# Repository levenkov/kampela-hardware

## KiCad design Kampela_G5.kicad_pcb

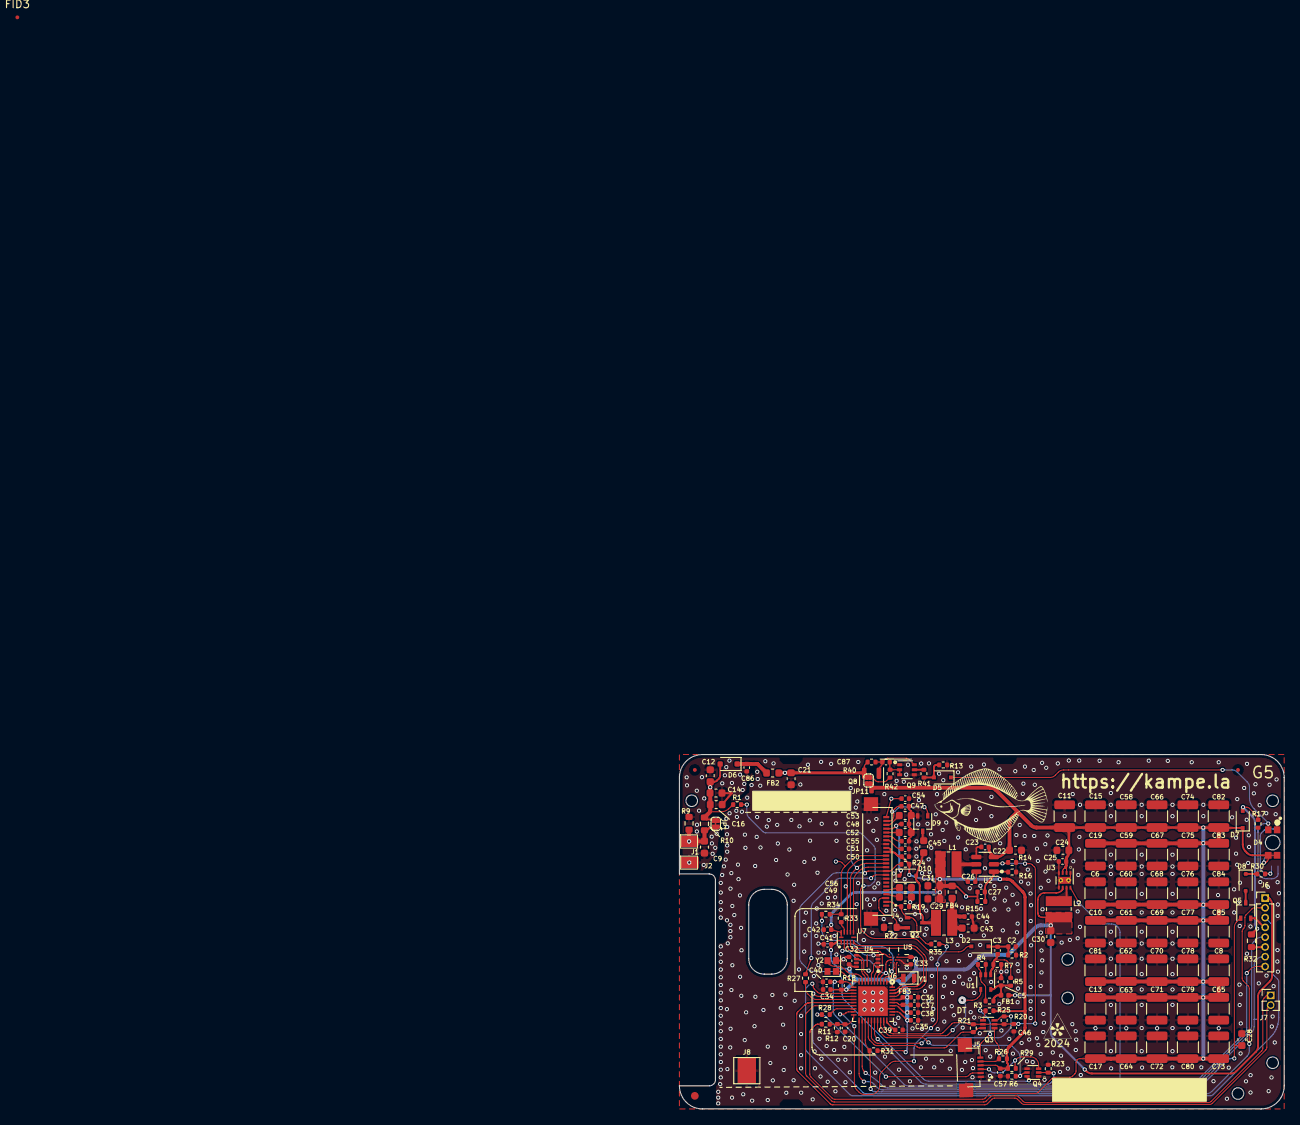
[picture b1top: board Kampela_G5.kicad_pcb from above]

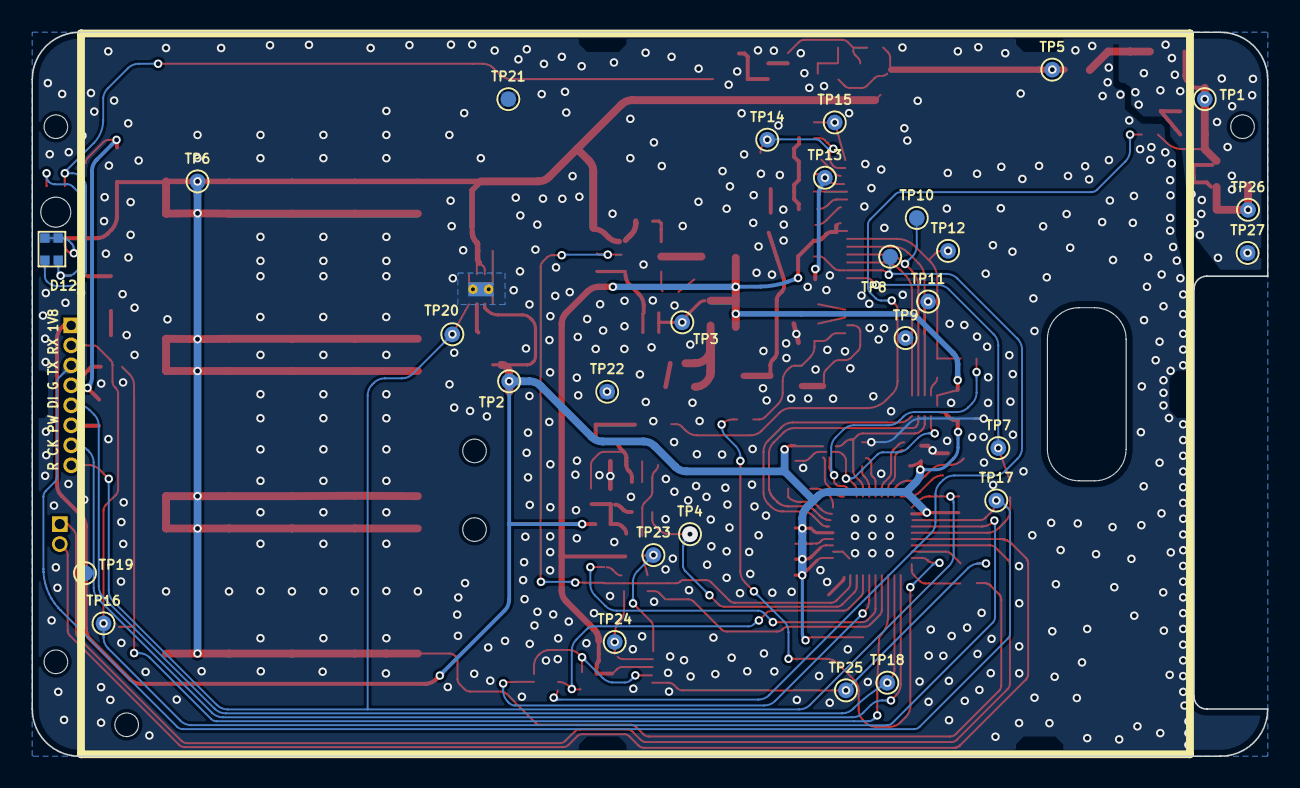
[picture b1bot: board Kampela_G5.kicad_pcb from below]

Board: 2 copper layers, 78.5 x 46.0 mm, 194 parts (28 on the bottom side), 86 nets.

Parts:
C2, C3, C27: 100p; C_0402_1005Metric
C5, C20, C23, C25, C26, C32, C33, C35, C36, C37, C38, C40, C41, C42, C46: 0.1u; C_0402_1005Metric
C6, C8, C10, C11, C13, C15, C17, C19, C58, C59, C60, C61, C62, C63, C64, C65, C66, C67, C68, C69, C70, C71, C72, C73, C74, C75, C76, C77, C78, C79, C80, C81, C82, C83, C84, C85: 47x16; C_1210_3225Metric
C9: 15p; C_0603_1608Metric
C12, C14: 47; C_0603_1608Metric
C16: 100; C_0603_1608Metric
C21: 10x25; C_0603_1608Metric
C22, C24: 10x16; C_0603_1608Metric
C28, C43, C45, C49, C52, C53, C56: 4.7x25; C_0603_1608Metric
C29, C30, C31: 22x6.3; C_0603_1608Metric
C34, C39, C50, C51, C55, C57: 1x6.3; C_0402_1005Metric
C44: 0.1; C_0402_1005Metric
C47, C48, C54, C86, C87: 1x50; C_0402_1005Metric
D2, D7, D10: BAT54WS; D_SOD-323F
D4: 156125RG73000; SMD4_WL-SBRW-1205_REV-MOUNT_WRE
D5: D3Z13BF-7; D_SOD-323F
D6: BAS70WS; D_SOD-323F
D8: D3Z5V1BF-7; D_SOD-323F
D9: BAS70-04W; SOT-323_SC-70
D12: SB0603WC01-RG; LED_DUAL_0603
FB1, FB3: BLM15AG102SZ1D; L_0402_1005Metric
FB2, FB4: BLM18KG102SN1D; L_0603_1608Metric
FID1, FID2, FID3, FID4: Fiducial; Fiducial_0.5mm_Mask1.5mm
H1, H2, H3: MountingHole; MountingHole_2.1mm
J1, J2, J8: E_ANT; TestPoint_Pad_2.4x3.5mm
J4: E2154CS0C1; GDEY027T91-T01_bended
J5: TOUCH; HRS_FH34SRJ-6S-0.5SH(50)
J6: Conn_01x08; PinHeader_1x08_P1.27mm_Vertical
J7: Conn_01x02; PinHeader_1x02_P1.27mm_Vertical
JP1, JP11: SolderJumper_2_Open; SolderJumper_0.8.x1mm
L1: 3.3uH; L_Wuerth_MAPI-3015
L2: 2.2uH; L_Wuerth_MAPI-3015
L3: NR3015T100M; L_Wuerth_MAPI-3015
Q2: PMF250XNEX; SOT-323_SC-70
Q3, Q4: SSM6N35AFE; SOT-563
Q5: NX138BKWX; SOT-323_SC-70
Q8: NTR5105PT1G; SOT-23
Q9: BC846BS; SOT-363_SC-70-6
R1, R6, R17, R18, R23, R24, R25, R26, R27, R28, R29: 10K; R_0402_1005Metric
R2, R3, R16: 52.3K; R_0402_1005Metric
R4, R41: 47K; R_0402_1005Metric
R5, R7, R40, R42: 100K; R_0402_1005Metric
R9: 1K; R_0603_1608Metric
R10, R32: 2.2; R_0603_1608Metric
R11: 976K; R_0402_1005Metric
R12, R14: 150K; R_0402_1005Metric
R13, R20, R21, R34, R35: 1K; R_0402_1005Metric
R15: 130K; R_0402_1005Metric
R19, R31: 470K; R_0402_1005Metric
R22: 0.47R; R_0603_1608Metric
R30, R33: 100; R_0402_1005Metric
TP1, TP2, TP3, TP4, TP5, TP6, TP7, TP8, TP9, TP10, TP11, TP12, TP13, TP14, TP15, TP16, TP17, TP18, TP19, TP20, TP21, TP22, TP23, TP24, TP25, TP26, TP27: TestPoint; TestPoint_Pad_D1.0mm
U1: LMV7271; SOT-353_SC-70-5
U2: AP63200WU; TSOT-23-6
U3: TPS62171DSG; WSON-8-1EP_2x2mm_P0.5mm_EP0.9x1.6mm_ThermalVias
U4: APS6404L-SQN; SON-8-1EP_3x2mm_P0.5mm_EP1.4x1.6mm
U5: AT25XE321D-UUN-T; WLCSP 12-ball 3 x 2 x 3 Array
U6: EFM32PG23B200F512IM40; QFN-40_EP_5x5_Pitch0.4mm
U7: TXU0104PW; Texas_R-PUQFN-N12
Y1: FC2012AN; Crystal_SMD_2012-2Pin_2.0x1.2mm
Y2: 39MHz; Crystal_SMD_2016-4Pin_2.0x1.6mm

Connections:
+1V8: C30.2, C32.1, C33.1, C34.2, C35.1, C36.1, C38.1, C41.2, FB1.1, FB3.2, J6.1, L2.2, R18.2, R31.1, TP2.1, U3.6 (VOS), U4.8 (VCC), U5.B2 (VCC), U6.12 (DVDD), U6.32 (VREGVDD), U6.34 (DVDD), U6.36 (IOVDD), U7.1 (VCCA)
+2V8: C27.1, C29.2, C31.2, C42.1, C50.2, C57.1, FB4.2, J4.15, J4.16, J5.4, L1.2, R15.1, R24.2, R25.1, R26.1, R29.2, TP3.1, U7.11 (VCCB), U7.12 (OE)
/Cap Block/HV: C6.2, C8.2, C10.2, C11.2, C13.2, C15.2, C17.2, C19.2, C22.2, C23.1, C24.2, C25.1, C58.2, C59.2, C60.2, C61.2, C62.2, C63.2, C64.2, C65.2, C66.2, C67.2, C68.2, C69.2, C70.2, C71.2, C72.2, C73.2, C74.2, C75.2, C76.2, C77.2, C78.2, C79.2, C80.2, C81.2, C82.2, C83.2, C84.2, C85.2, D4.3 (A2), D4.4 (A1), D7.1 (K), D12.2 (K1), D12.4 (K2), JP11.1 (A), Q8.3 (D), R11.1, TP6.1, U2.3 (IN), U3.2 (VIN), U3.3 (EN)
/Display/2V8_EN: C46.1, Q3.2 (G), Q3.5 (G), R14.2, R20.2, R21.2, U2.2 (EN), U6.29 (PA09)
/Display/BUSY: R27.2, U6.15 (PB04)
/Display/E_BUSY: J4.9, R27.1, TP7.1
/Display/E_CS: U6.38 (PD02), U7.4 (A3)
/Display/E_D/C: U6.37 (PD03), U7.5 (A4)
/Display/E_MISO: R34.1, U5.D4 (IO1/SO), U6.2 (PC01)
/Display/E_RES: J4.10, Q4.6 (D), R24.1, TP8.1
/Display/E_SCK: U5.F2 (SCK), U6.4 (PC03), U7.3 (A2)
/Display/E_SDI: U5.E3 (SI/IO0), U6.3 (PC02), U7.2 (A1)
/Display/GDR: J4.2, Q2.1 (G), R19.1, R35.1
/Display/H_CS: J4.12, TP10.1, U7.8 (B3)
/Display/H_D/C: J4.11, TP9.1, U7.7 (B4)
/Display/H_SCK: J4.13, TP11.1, U7.9 (B2)
/Display/H_SDI: J4.14, R33.1, R34.2, TP12.1
/Display/INT: R28.2, U6.18 (PB01)
/Display/POW: C43.2, C44.1, FB4.1, L3.1
/Display/PREVGH: C48.1, D10.1 (K), J4.21, TP13.1
/Display/PREVGL: C47.1, D9.1, J4.23, TP14.1
/Display/RES: Q4.2 (G), R23.2, U6.26 (PA06)
/Display/RESE: J4.3, Q2.2 (S), R22.1
/Display/RES_TC: Q4.5 (G), R6.2, U6.27 (PA07)
/Display/SCL: Q3.3 (D), R21.1, U6.24 (PA04)
/Display/SDA: Q3.6 (D), R20.1, U6.25 (PA05)
/Display/T_INT: J5.2, R28.1, TP25.1
/Display/T_RES: J5.3, Q4.3 (D), R29.1
/Display/T_SCL: J5.5, Q3.4 (S), R26.2, TP24.1
/Display/T_SDA: J5.6, Q3.1 (S), R25.2, TP23.1
/Display/VCOM: C54.2, J4.24, TP15.1
/MCU/DATA: TP4.1, U1.4, U6.28 (PA08)
/MCU/FLASH_CS: U5.B4 (~CS), U6.1 (PC00)
/MCU/P_GOOD: C40.1, J6.8, R18.1, TP20.1, U3.8 (PG), U6.11 (~RESET)
/MCU/P_IN: J6.6, R32.1
/MCU/RAM_CS: U4.1 (~CE), U6.5 (PC04)
/MCU/RX: J6.2, TP16.1, U6.14 (PB05)
/MCU/R_MISO: U4.2 (SO/SIO), U6.6 (PC05)
/MCU/R_MOSI: U4.5 (SI/SIO), U6.7 (PC06)
/MCU/R_SCK: U4.6 (SCLK), U6.8 (PC07)
/MCU/SWDCK: J6.7, TP19.1, U6.21 (PA01)
/MCU/SWDIO: J6.5, TP18.1, U6.22 (PA02)
/MCU/TX: J6.3, TP17.1, U6.13 (PB06)
/MCU/V_CHK: C20.1, R11.2, R12.1, U6.20 (PA00)
/MCU/~MCU_OK: C28.2, Q5.1 (G), R31.2, U6.23 (PA03)
/Power/IN_DT: C12.1, C14.1, C16.1, D6.2 (A), JP1.1 (A), R1.1, R10.2, TP1.1
GND: C2.2, C5.1, C6.1, C8.1, C9.2, C10.1, C11.1, C12.2, C13.1, C14.2, C15.1, C16.2, C17.1, C19.1, C20.2, C21.1, C22.1, C23.2, C24.1, C25.2, C28.1, C29.1, C30.1, C31.1, C32.2, C33.2, C34.1, C35.2, C36.2, C37.2, C38.2, C39.1, C40.2, C41.1, C42.2, C43.1, C44.2, C46.2, C47.2, C48.2, C49.1, C50.1, C51.1, C52.1, C53.1, C54.1, C55.1, C56.1, C57.2, C58.1, C59.1, C60.1, C61.1, C62.1, C63.1, C64.1, C65.1, C66.1, C67.1, C68.1, C69.1, C70.1, C71.1, C72.1, C73.1, C74.1, C75.1, C76.1, C77.1, C78.1, C79.1, C80.1, C81.1, C82.1, C83.1, C84.1, C85.1, C86.2, D9.2, J2.1, J4.8, J4.17, J4.S2 (S), J5.1, J5.S2 (S), J6.4, J8.1, Q4.1 (S), Q4.4 (S), Q5.2 (S), Q9.1 (E1), Q9.4 (E2), R2.2, R4.2, R6.1, R7.2, R9.1, R12.2, R13.2, R14.1, R16.2, R17.2, R19.2, R22.2, R23.1, TP21.1, TP22.1, TP27.1, U1.2 (V-), U2.4 (GND), U3.1 (PGND), U3.4 (AGND), U3.5 (FB), U3.9 (PAD), U4.4 (VSS), U5.C3 (GND), U6.33 (VREGVSS), U6.41 (VSS), U7.6 (GND), Y2.2
unnamed: C45.1, D9.3
unnamed: D2.2 (A), R1.2
unnamed: C2.1, C3.2, D2.1 (K), R2.1
unnamed: D5.2 (A), R13.1, R41.2
unnamed: C86.1, D6.1 (K), FB2.2
unnamed: D7.2 (A), R17.1, R32.2
unnamed: D8.2 (A), Q5.3 (D)
unnamed: D8.1 (K), R30.2
unnamed: C45.2, D10.2 (A), L3.2, Q2.3 (D)
unnamed: D4.2 (K2), D5.1 (K), D12.1 (A1)
unnamed: D4.1 (K1), D12.3 (A2), R30.1
unnamed: C9.1, J1.1, JP1.2 (B), R9.2, R10.1, TP26.1
unnamed: C49.2, J4.4
unnamed: C56.2, J4.5
unnamed: C51.2, J4.18
unnamed: C55.2, J4.19
unnamed: C52.2, J4.20
unnamed: C53.2, J4.22
unnamed: J7.1, U6.17 (PB02)
unnamed: J7.2, U6.16 (PB03)
unnamed: C21.2, FB2.1, JP11.2 (B), Q8.2 (S), R40.1, R42.1, TP5.1
unnamed: C87.1, Q8.1 (G), Q9.6 (C1), R40.2
unnamed: C87.2, Q9.2 (B1), Q9.3 (C2), R42.2
unnamed: Q9.5 (B2), R41.1
unnamed: C3.1, R5.2, R7.1, U1.1 (+)
unnamed: R3.2, R4.1, U1.3 (-)
unnamed: C5.2, FB1.2, R3.1, R5.1, U1.5 (V+)
unnamed: C26.2, U2.6 (BST)
unnamed: C27.2, R15.2, R16.1, U2.1 (FB)
unnamed: C26.1, L1.1, U2.5 (SW)
unnamed: L2.1, U3.7 (SW)
unnamed: C37.1, FB3.1, U6.35 (AVDD)
unnamed: C39.2, U6.30 (CAP)
unnamed: U6.9 (HFXTAL_I), Y2.3
unnamed: U6.10 (HFXTAL_O), Y2.1
unnamed: R35.2, U6.19 (PB00)
unnamed: U6.40 (PD00), Y1.2
unnamed: U6.39 (PD01), Y1.1
unnamed: R33.2, U7.10 (B1)

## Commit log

2025-11-19 Fix capacitor values
2025-11-19 Fill up mouser part numbers
2025-11-20 Finish BOM components filling
2025-11-26 Cleanup and add display datasheet
2025-12-05 Fix BOM
